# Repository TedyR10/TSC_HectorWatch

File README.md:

**Name: Theodor-Ioan Rolea**

**Group: 333CA**

# Hector Watch

### Description
* This project focuses on creating a smart watch from the ground up using
certain parts provided by the TSC Team. The smart watch has the following
features: 6 axis intertial unit, haptic motor driver, LiPo battery,
USB C, 1.28 inch 240x240p LCD display.

***

### Steps to developing the watch
* 1. Electrical scheme implementation
* 2. PCB design

***

### Electrical scheme implementation
* The provided electrical scheme was implemented using Fusion 360's schematic feature,
then the components were linked to the PCB design.

***

### PCB design
* The PCB design was done using Fusion 360's PCB design feature. The routes were done
manually, routing with 0.3mm for the power lines and 0.127mm for the signal lines. I
decided not to place the test pads in a specific location, but rather place them in
a way that would allow me to fully connect the components.

***

### Final thoughts
* The project was a great experience, as it allowed me to learn how to use Fusion 360's
schematic and PCB design features. I also learned how to properly route the PCB and
how to properly place the components. I am looking forward to the next project.

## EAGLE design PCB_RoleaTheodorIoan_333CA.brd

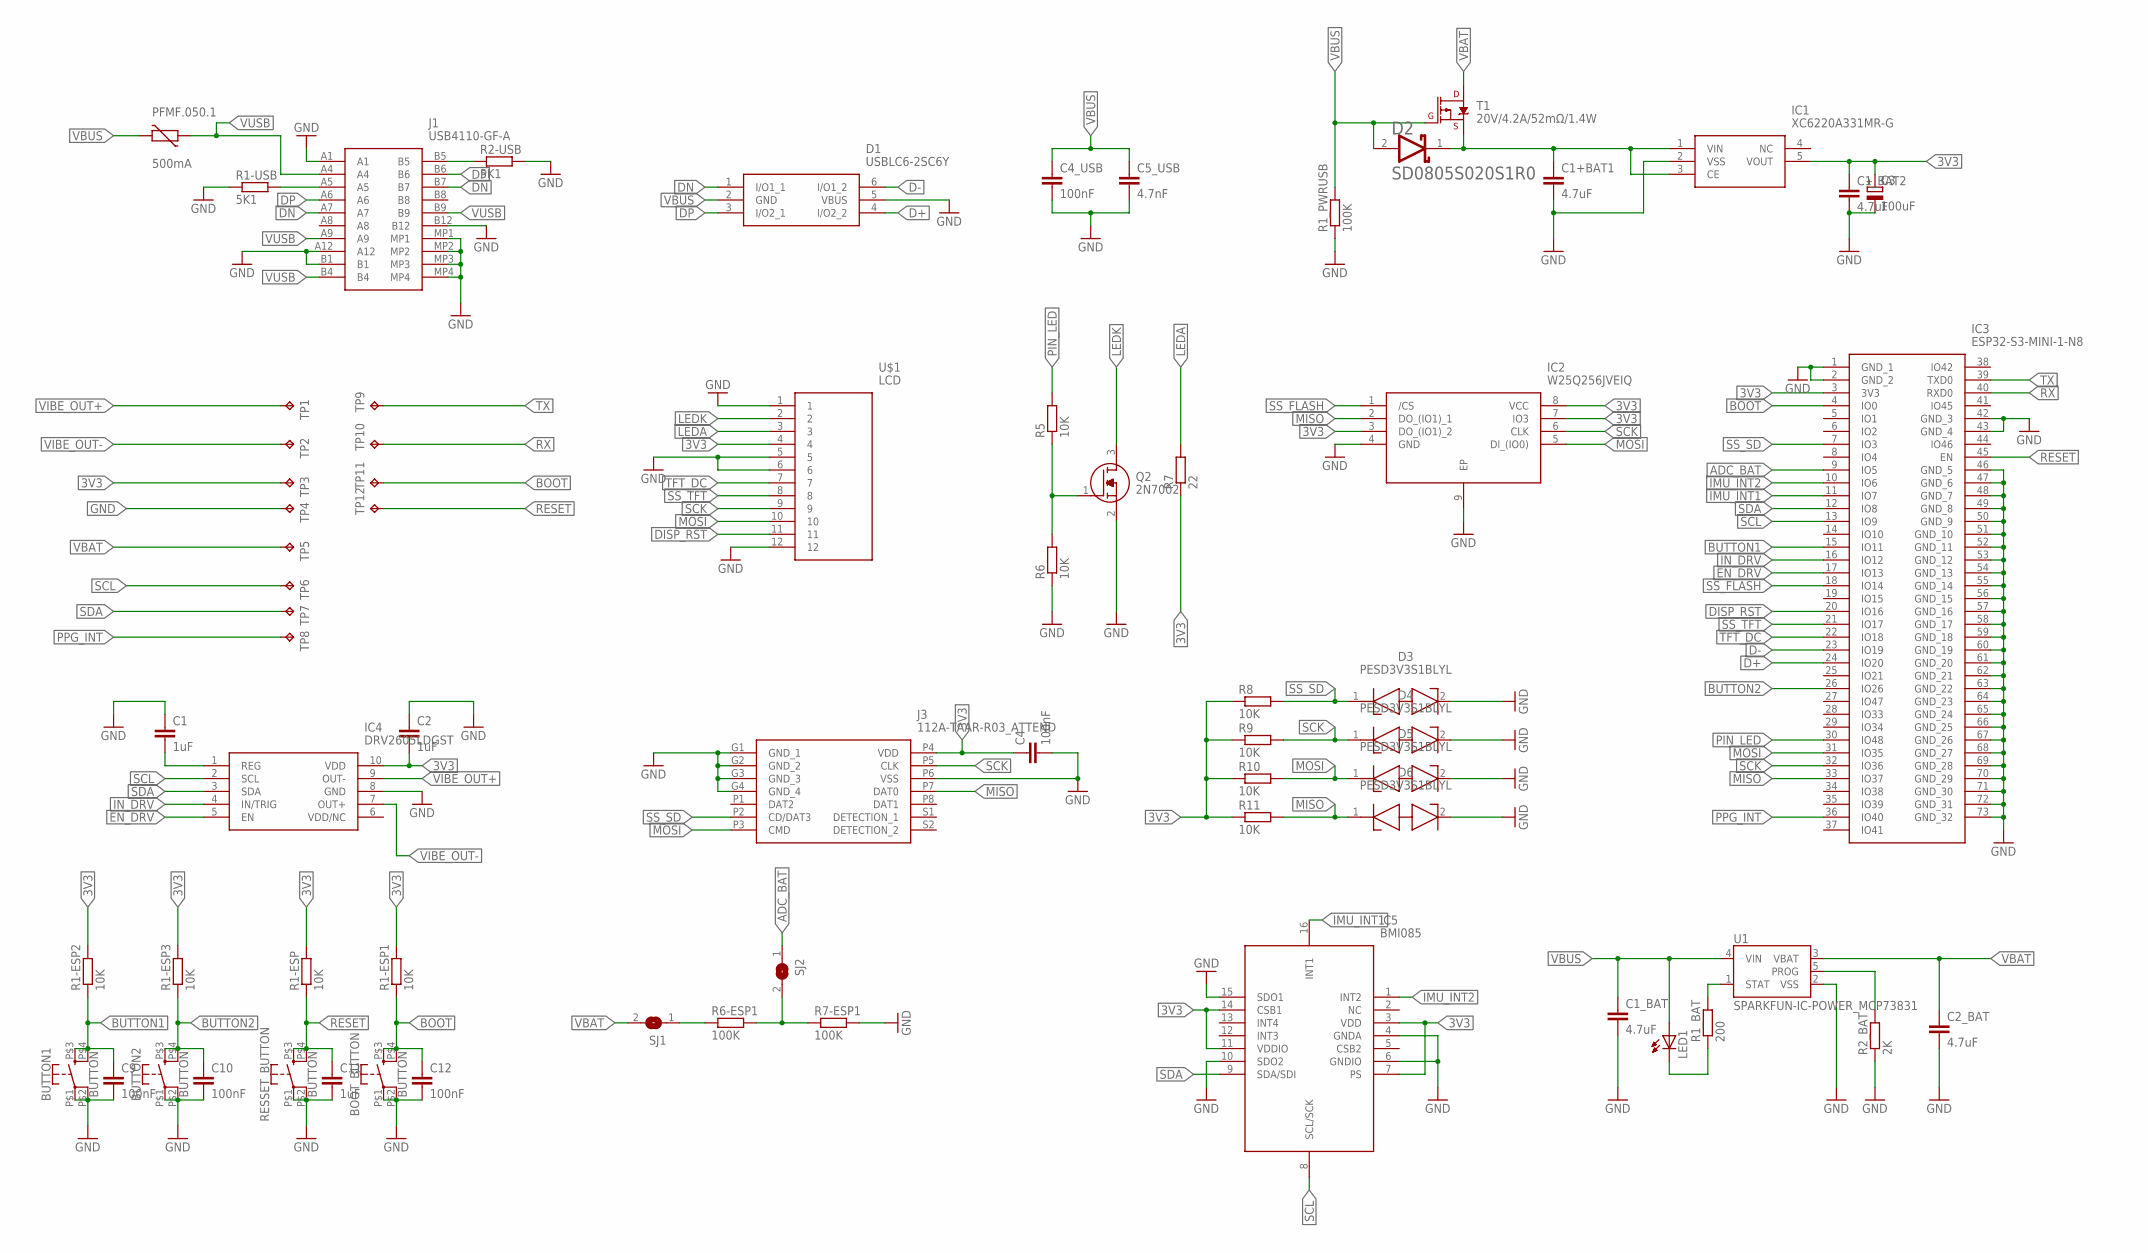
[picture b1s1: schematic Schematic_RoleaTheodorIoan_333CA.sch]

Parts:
BOOT_BUTTON: BUTTON
BUTTON1, BUTTON2: BUTTON
C1, C2, C11: 1uF; EAGLE-LTSPICE_C0402
C1+BAT1, C1_BAT, C1_BAT2, C2_BAT: 4.7uF; RCL_C0603
C3: 100uF; CT3528
C4, C9, C10, C12: 100nF; EAGLE-LTSPICE_C0402
C4_USB: 100nF; RCL_C0603
C5_USB: 4.7nF; RCL_C0603
D1: USBLC6-2SC6Y; SOT95P280X145-6N
D2: AVX---SD0805S020S1R0_AVX_SD0805S020S1R0AVX_SD0805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; AVX---SD0805S020S1R0_AVX_SD0805S020S1R0_0
D3, D4, D5, D6: PESD3V3S1BLYL; PESD5V0S1BL315
IC1: XC6220A331MR-G; SOT95P280X120-5N
IC2: W25Q256JVEIQ; SON127P800X600X80-9N
IC3: ESP32-S3-MINI-1-N8; ESP32S3MINI1N8
IC4: DRV2605LDGST; SOP50P490X110-10N
IC5: BMI085
J1: USB4110-GF-A; USB4110GFA
J3: 112A-TAAR-R03_ATTEND; 112ATAARR03ATTEND
LED1: ADAFRUIT_LEDCHIP-LED0603; ADAFRUIT_CHIP-LED0603
PFMF.050.1: 500mA; VARISTOR_CT/CN1812
Q2: 2N7002; SOT96P240X120-3N
R1-ESP, R1-ESP1, R1-ESP2, R1-ESP3, R5, R6, R8, R9, R10, R11: 10K; EAGLE-LTSPICE_R0402
R1-USB, R2-USB: 5K1; EAGLE-LTSPICE_R0402
R1_BAT: 200; EAGLE-LTSPICE_R0402
R1_PWRUSB, R6-ESP1, R7-ESP1: 100K; EAGLE-LTSPICE_R0402
R2_BAT: 2K; EAGLE-LTSPICE_R0402
R7: 22; EAGLE-LTSPICE_R0402
RESSET_BUTTON: BUTTON
SJ1, SJ2: SJ
T1: 20V/4.2A/52mΩ/1.4W; SPARKFUN-DISCRETESEMI_SOT23-3
TP1, TP2, TP3, TP4, TP5, TP6, TP7, TP8, TP9, TP10, TP11, TP12: TPTP20R; TP20R
U1: SPARKFUN-IC-POWER_MCP73831; SPARKFUN-IC-POWER_SOT23-5
U$1: LCD; LCD_CONNECTOR

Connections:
3V3: C1_BAT2.1, C2.2, C3.+, C4.1, IC1.5 (VOUT), IC2.3 (DO_(IO1)_2), IC2.7 (IO3), IC2.8 (VCC), IC3.3 (3V3), IC4.10 (VDD), IC5.3 (VDD), IC5.7 (PS), IC5.11 (VDDIO), IC5.14 (CSB1), J3.P4 (VDD), R1-ESP.2, R1-ESP1.2, R1-ESP2.2, R1-ESP3.2, R7.1, R8.1, R9.1, R10.1, R11.1, TP3.TP, U$1.4
ADC_BAT: IC3.9 (IO5), SJ2.1
BOOT: BOOT_BUTTON.P$3 (3), BOOT_BUTTON.P$4 (4), C12.1, IC3.4 (IO0), R1-ESP1.1, TP11.TP
BUTTON1: BUTTON1.P$3 (3), BUTTON1.P$4 (4), C9.1, IC3.15 (IO11), R1-ESP2.1
BUTTON2: BUTTON2.P$3 (3), BUTTON2.P$4 (4), C10.1, IC3.26 (IO26), R1-ESP3.1
D+: D1.4 (I/O2_2), IC3.24 (IO20)
D-: D1.6 (I/O1_2), IC3.23 (IO19)
DISP_RST: IC3.20 (IO16), U$1.11
DN: D1.1 (I/O1_1), J1.A7, J1.B7
DP: D1.3 (I/O2_1), J1.A6, J1.B6
EN_DRV: IC3.17 (IO13), IC4.5 (EN)
GND: BOOT_BUTTON.P$1 (1), BOOT_BUTTON.P$2 (2), BUTTON1.P$1 (1), BUTTON1.P$2 (2), BUTTON2.P$1 (1), BUTTON2.P$2 (2), C1.1, C1+BAT1.2, C1_BAT.2, C1_BAT2.2, C2.1, C2_BAT.2, C3.-, C4.2, C4_USB.2, C5_USB.2, C9.2, C10.2, C11.2, C12.2, D1.5 (VBUS), D3.2 (K2), D4.2 (K2), D5.2 (K2), D6.2 (K2), IC1.2 (VSS), IC2.4 (GND), IC2.9 (EP), IC3.1 (GND_1), IC3.2 (GND_2), IC3.42 (GND_3), IC3.43 (GND_4), IC3.46 (GND_5), IC3.47 (GND_6), IC3.48 (GND_7), IC3.49 (GND_8), IC3.50 (GND_9), IC3.51 (GND_10), IC3.52 (GND_11), IC3.53 (GND_12), IC3.54 (GND_13), IC3.55 (GND_14), IC3.56 (GND_15), IC3.57 (GND_16), IC3.58 (GND_17), IC3.59 (GND_18), IC3.60 (GND_19), IC3.61 (GND_20), IC3.62 (GND_21), IC3.63 (GND_22), IC3.64 (GND_23), IC3.65 (GND_24), IC3.66 (GND_25), IC3.67 (GND_26), IC3.68 (GND_27), IC3.69 (GND_28), IC3.70 (GND_29), IC3.71 (GND_30), IC3.72 (GND_31), IC3.73 (GND_32), IC4.8 (GND), IC5.4 (GNDA), IC5.6 (GNDIO), IC5.10 (SDO2), IC5.15 (SDO1), J1.A1, J1.A12, J1.B1, J1.B12, J1.MP1, J1.MP2, J1.MP3, J1.MP4, J3.G1 (GND_1), J3.G2 (GND_2), J3.G3 (GND_3), J3.G4 (GND_4), J3.P6 (VSS), Q2.2 (S), R1-USB.1, R1_PWRUSB.1, R2-USB.2, R2_BAT.1, R6.1, R7-ESP1.2, RESSET_BUTTON.P$1 (1), RESSET_BUTTON.P$2 (2), TP4.TP, U1.2 (VSS), U$1.1, U$1.5, U$1.6, U$1.12
IMU_INT1: IC3.11 (IO7), IC5.16 (INT1)
IMU_INT2: IC3.10 (IO6), IC5.1 (INT2)
IN_DRV: IC3.16 (IO12), IC4.4 (IN/TRIG)
LEDA: R7.2, U$1.3
LEDK: Q2.3 (D), U$1.2
MISO: D6.1 (K1), IC2.2 (DO_(IO1)_1), IC3.33 (IO37), J3.P7 (DAT0), R11.2
MOSI: D5.1 (K1), IC2.5 (DI_(IO0)), IC3.31 (IO35), J3.P3 (CMD), R10.2, U$1.10
unnamed: J1.B5, R2-USB.1
unnamed: R6-ESP1.1, SJ1.1
unnamed: C1+BAT1.1, D2.1 (CATHODE), IC1.1 (VIN), IC1.3 (CE), T1.2 (S)
unnamed: C1.2, IC4.1 (REG)
unnamed: Q2.1 (G), R5.1, R6.2
unnamed: R6-ESP1.2, R7-ESP1.1, SJ2.2
unnamed: R1_BAT.2, U1.1 (STAT)
unnamed: R2_BAT.2, U1.5 (PROG)
unnamed: J1.A5, R1-USB.2
unnamed: LED1.C, R1_BAT.1
PIN_LED: IC3.30 (IO48), R5.2
PPG_INT: IC3.36 (IO40), TP8.TP
RESET: C11.1, IC3.45 (EN), R1-ESP.1, RESSET_BUTTON.P$3 (3), RESSET_BUTTON.P$4 (4), TP12.TP
RX: IC3.40 (RXD0), TP10.TP
SCK: D4.1 (K1), IC2.6 (CLK), IC3.32 (IO36), J3.P5 (CLK), R9.2, U$1.9
SCL: IC3.13 (IO9), IC4.2 (SCL), IC5.8 (SCL/SCK), TP6.TP
SDA: IC3.12 (IO8), IC4.3 (SDA), IC5.9 (SDA/SDI), TP7.TP
SS_FLASH: IC2.1 (/CS), IC3.18 (IO14)
SS_SD: D3.1 (K1), IC3.7 (IO3), J3.P2 (CD/DAT3), R8.2
SS_TFT: IC3.21 (IO17), U$1.8
TFT_DC: IC3.22 (IO18), U$1.7
TX: IC3.39 (TXD0), TP9.TP
VBAT: C2_BAT.1, SJ1.2, T1.3 (D), TP5.TP, U1.3 (VBAT)
VBUS: C1_BAT.1, C4_USB.1, C5_USB.1, D1.2 (GND), D2.2 (ANODE), LED1.A, PFMF.050.1.2, R1_PWRUSB.2, T1.1 (G), U1.4 (VIN)
VIBE_OUT+: IC4.9 (OUT-), TP1.TP
VIBE_OUT-: IC4.7 (OUT+), TP2.TP
VUSB: J1.A4, J1.A9, J1.B4, J1.B9, PFMF.050.1.1

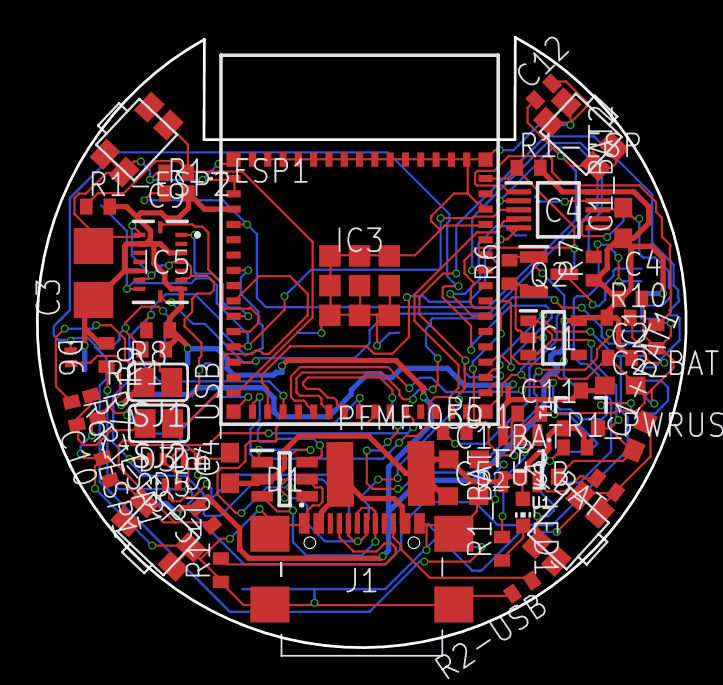
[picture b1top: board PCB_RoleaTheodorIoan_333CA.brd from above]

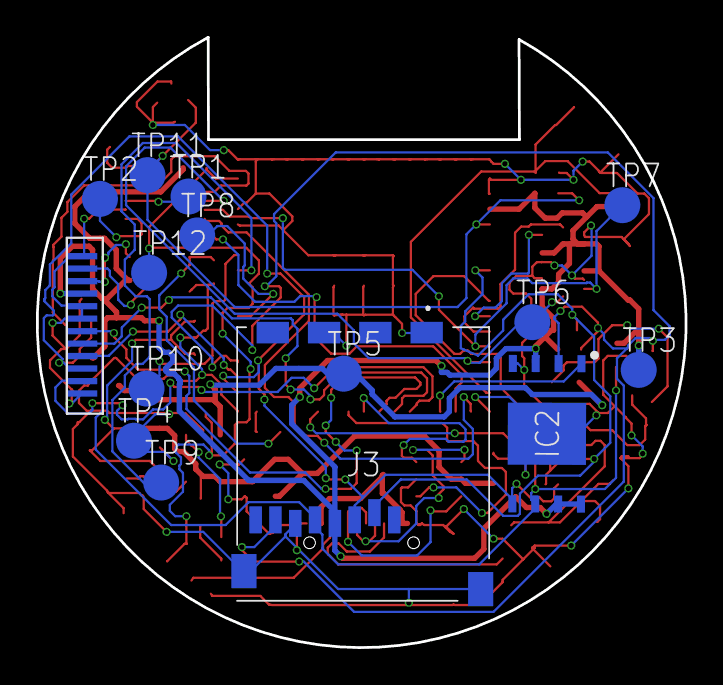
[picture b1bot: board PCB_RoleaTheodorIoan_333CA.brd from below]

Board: 2 copper layers, 36.0 x 33.9 mm, 69 parts (15 on the bottom side), 46 nets.
